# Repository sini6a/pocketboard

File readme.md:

# Pocketboard

### A Pocket-Friendly On-the-Go Keyboard 🖲️

**Pocketboard** is a compact, versatile keyboard designed for IT technicians and professionals who need a portable and efficient input device.

**NOTE:** If you are building this keyboard and want to use KMK make sure to flash MicroPython for [Adafruit Feather RP2040](https://micropython.org/download/ADAFRUIT_FEATHER_RP2040/). After flashing just copy and paste the firmware located in the `firmware/kmk` folder. I recommend using the QMK firmware instead of KMK.

## Progress List:

- [x] Firmware: Home row mods!
- [x] Firmware: Layers
- [x] Firmware: LED Control (On/Off)
- [x] Hardware & Firmware: LCD!
- [x] 3D: Case Design

## Features

- **USB Type-C Connector**: Modern and reliable connection for seamless usage.
- **Miryoku Layout**: Optimized for productivity and efficient typing.
- **LEDs and Display**: Equipped with programmable LEDs and a display which shows pressed key and small animation when idle.

## What's New?

Pocketboard builds upon the original **HandiPi** design with several upgrades and enhancements:

- **ATMega328 replaced with RP2040**: Improved performance and more flexibility with the powerful RP2040 microcontroller.
- **LEDs for Illumination**: Added for better visibility.
- **USB Type-C Connector**: Ensures ease of connectivity and compatibility with modern devices.
- **LCD Support**: Added support for an LCD display for dynamic functionality. Tested and fully operational!
- **SMD Components**: Transitioned from through-hole components to SMD for a more compact design.

## Why Pocketboard?

Pocketboard is crafted for those who are often on the move, combining portability with practicality. Whether you're debugging systems or managing configurations, this handy keyboard ensures you're always prepared and comes handy to keep in your cargo pants or in your car.

## Project Structure

The project repository is structured as follows:

- **`kicad/`**: Contains PCB design files and schematics.
- **`gerbers/`**: Includes Gerber files essential for manufacturing.
- **`fimware/qmk`**: Includes Pocketboard firmware files. This folder should be copied to `qmk_firmware/keyboards`  before compiling.
- **`fimware/kmk`**: Includes Pocketboard firmware files. This folder should be copied to your keyboard after flashing MicroPython. (Not fully implemented!)

The schematic is available in PDF format in the `kicad/` directory.

## Credits

Pocketboard is inspired by the **HandiPi** project by [brickbots](https://github.com/brickbots).

## Contributing

We welcome contributions from the community! If you’re interested in helping with development, please:

1. Open an issue to discuss your ideas or proposed changes.
2. After discussion, submit a pull request (PR) with your contribution.

Your feedback and suggestions are invaluable in making Pocketboard even better!

## Support

If you find this project useful, please consider buying from us:

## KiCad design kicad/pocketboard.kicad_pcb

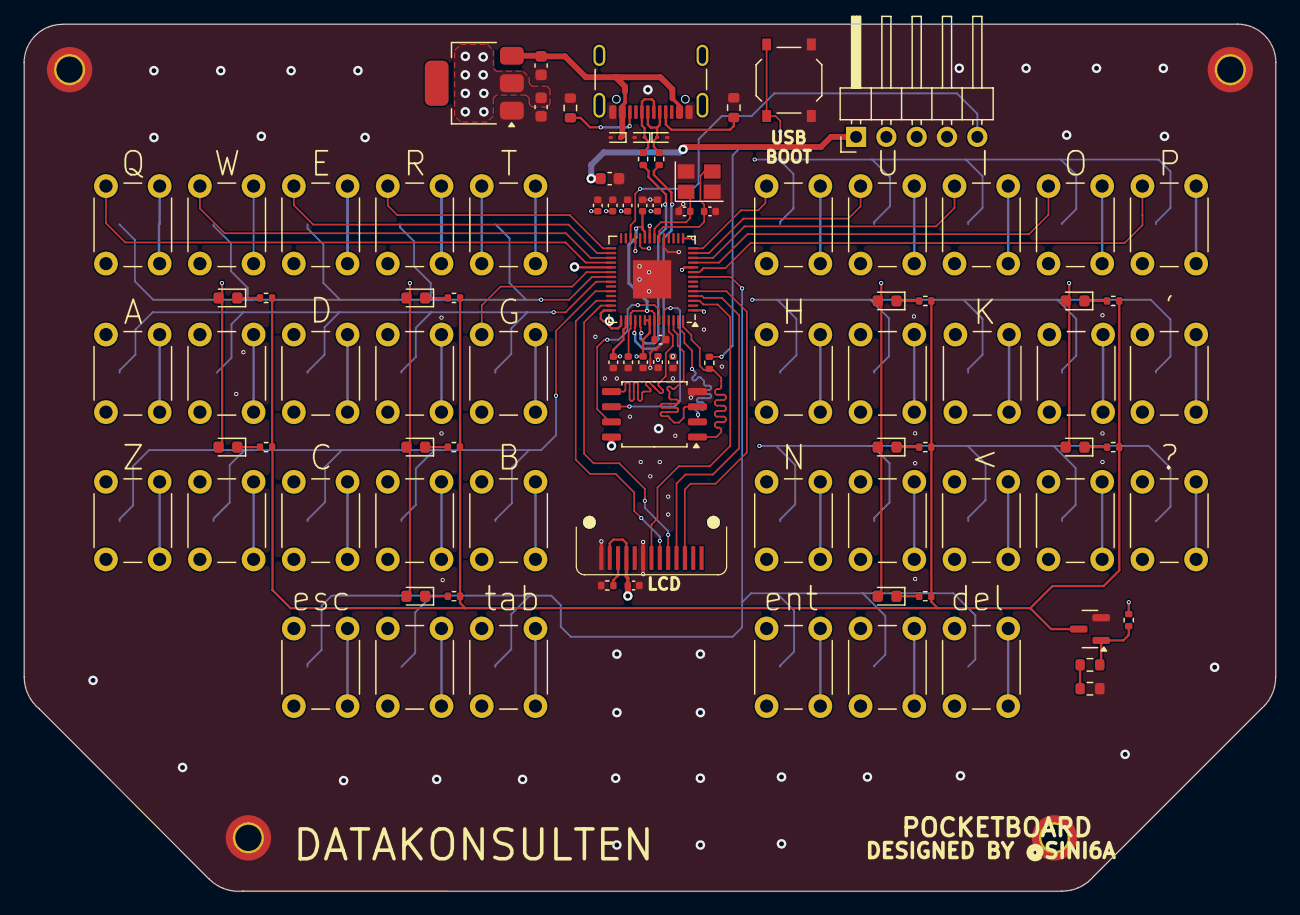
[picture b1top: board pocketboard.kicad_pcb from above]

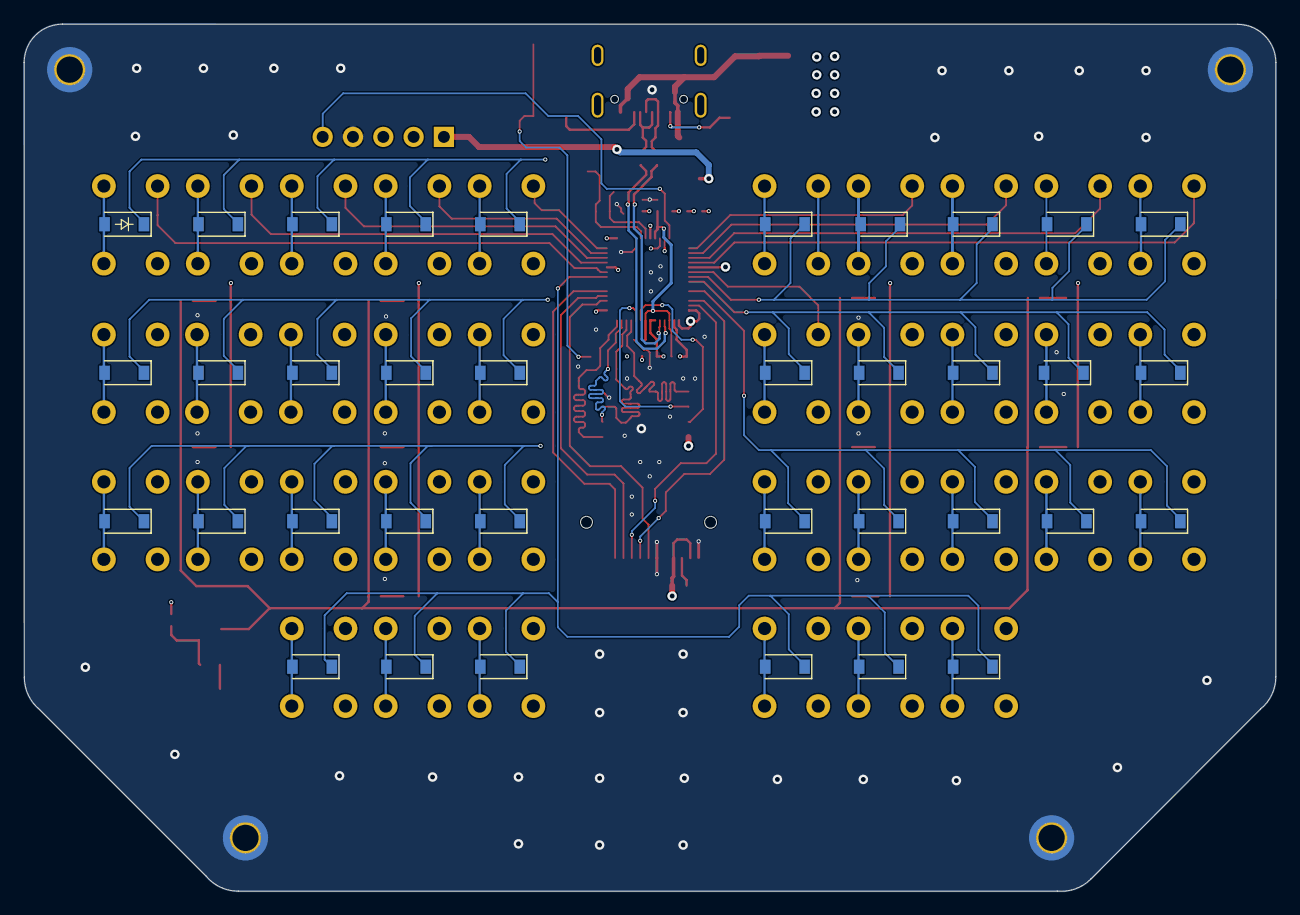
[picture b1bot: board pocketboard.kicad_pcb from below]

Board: 4 copper layers, 104.9 x 72.7 mm, 134 parts (36 on the bottom side), 92 nets.

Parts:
C201, C202, C312: 10u; C_0603_1608Metric
C301, C302, C305, C306, C307, C308, C309, C310, C311, C501: 100n; C_0402_1005Metric
C303, C304: 1u; C_0402_1005Metric
C313, C314: 33p; C_0402_1005Metric
D1, D2, D3: D_Zener; D_SOD-923
D301, D302, D303, D304, D305, D306, D307, D308, D309, D310: LED; LED_0603_1608Metric
D401, D402, D403, D404, D405, D406, D407, D408, D409, D410, D411, D412, D413, D414, D415, D416, D417, D418, D419, D420, D421, D422, D423, D424, D425, D426, D427, D428, D429, D430, D431, D432, D433, D434, D435, D436: D; D_SOD-123
H1, H2, H3, H4: Hole_Pad; MountingHole_2.2mm_M2_DIN965_Pad_TopBottom
J1: USB_C_Receptacle_USB2.0_16P; USB_C_Receptacle_GCT_USB4105-xx-A_16P_TopMnt_Horizontal
J301: DEBUG_HEADER; PinHeader_1x05_P2.54mm_Horizontal
J501: Conn_01x13; N096-1608TBBIG11-H13
Q301: 2N7002; SOT-23
R1, R2, R315, R316: 5k1; R_0603_1608Metric
R301, R302: 27R; R_0402_1005Metric
R303, R314: 1k; R_0402_1005Metric
R304, R305, R306, R307, R308, R309, R310, R311, R312, R313, R503: 33R; R_0402_1005Metric
SW401, SW402, SW403, SW404, SW405, SW406, SW407, SW408, SW409, SW410, SW411, SW412, SW413, SW414, SW415, SW416, SW417, SW418, SW419, SW420, SW421, SW422, SW423, SW424, SW425, SW426, SW427, SW428, SW429, SW430, SW431, SW432, SW433, SW434, SW435, SW436: SW_Push_Dual; SW_PUSH_6mm
SW501: SW_Push_45deg; SW_Push_1P1T_XKB_TS-1187A
U201: NCP1117-3.3_SOT223; SOT-223
U301: RP2040; QFN-56-1EP_7x7mm_P0.4mm_EP3.2x3.2mm
U302: W25Q128JVS; SOIC-8_5.23x5.23mm_P1.27mm
Y301: 12MHz 20pF; Crystal_SMD_3225-4Pin_3.2x2.5mm

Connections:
+1V1: C301.1, C302.1, C303.1, U301.23 (DVDD), U301.45 (VREG_VOUT), U301.50 (DVDD)
+3V3: C202.1, C304.1, C305.1, C306.1, C307.1, C308.1, C309.1, C310.1, C311.1, C312.1, C501.1, D301.2 (A), D302.2 (A), D303.2 (A), D304.2 (A), D305.2 (A), D306.2 (A), D307.2 (A), D308.2 (A), D309.2 (A), D310.2 (A), J301.1, J501.10, J501.12, U201.2 (VO), U301.1 (IOVDD), U301.10 (IOVDD), U301.22 (IOVDD), U301.33 (IOVDD), U301.42 (IOVDD), U301.43 (ADC_AVDD), U301.44 (VREG_IN), U301.48 (USB_VDD), U301.49 (IOVDD), U302.8 (VCC)
/Keyboard Matrix/COL0: SW401.1, SW411.1, SW421.1, U301.32 (GPIO21)
/Keyboard Matrix/COL1: SW402.1, SW412.1, SW422.1, U301.31 (GPIO20)
/Keyboard Matrix/COL2: SW403.1, SW413.1, SW423.1, SW431.1, U301.30 (GPIO19)
/Keyboard Matrix/COL3: SW404.1, SW414.1, SW424.1, SW432.1, U301.29 (GPIO18)
/Keyboard Matrix/COL4: SW405.1, SW415.1, SW425.1, SW433.1, U301.34 (GPIO22)
/Keyboard Matrix/COL5: SW406.1, SW416.1, SW426.1, SW434.1, U301.14 (GPIO11)
/Keyboard Matrix/COL6: SW407.1, SW417.1, SW427.1, SW435.1, U301.13 (GPIO10)
/Keyboard Matrix/COL7: SW408.1, SW418.1, SW428.1, SW436.1, U301.12 (GPIO9)
/Keyboard Matrix/COL8: SW409.1, SW419.1, SW429.1, U301.11 (GPIO8)
/Keyboard Matrix/COL9: SW410.1, SW420.1, SW430.1, U301.9 (GPIO7)
/Keyboard Matrix/ROW0: D401.1 (K), D402.1 (K), D403.1 (K), D404.1 (K), D405.1 (K), D406.1 (K), D407.1 (K), D408.1 (K), D409.1 (K), D410.1 (K), U301.35 (GPIO23)
/Keyboard Matrix/ROW1: D411.1 (K), D412.1 (K), D413.1 (K), D414.1 (K), D415.1 (K), D416.1 (K), D417.1 (K), D418.1 (K), D419.1 (K), D420.1 (K), U301.36 (GPIO24)
/Keyboard Matrix/ROW2: D421.1 (K), D422.1 (K), D423.1 (K), D424.1 (K), D425.1 (K), D426.1 (K), D427.1 (K), D428.1 (K), D429.1 (K), D430.1 (K), U301.38 (GPIO26_ADC0)
/Keyboard Matrix/ROW3: D431.1 (K), D432.1 (K), D433.1 (K), D434.1 (K), D435.1 (K), D436.1 (K), U301.8 (GPIO6)
/LCD/D/C: J501.5, U301.41 (GPIO29_ADC3)
/LCD/LEDK: J501.11, R503.2
/LCD/SCL: J501.4, U301.4 (GPIO2)
/LCD/SDA: J501.3, U301.5 (GPIO3)
/LCD/~CS: J501.7, U301.3 (GPIO1)
/LCD/~RESET: J501.6, U301.40 (GPIO28_ADC2)
/Microcontroller/QSPI_SCLK: U301.52 (QSPI_SCLK), U302.6 (CLK)
/Microcontroller/QSPI_SD0: U301.53 (QSPI_SD0), U302.5 (DI(IO0))
/Microcontroller/QSPI_SD1: U301.55 (QSPI_SD1), U302.2 (DO(IO1))
/Microcontroller/QSPI_SD2: U301.54 (QSPI_SD2), U302.3 (IO2)
/Microcontroller/QSPI_SD3: U301.51 (QSPI_SD3), U302.7 (IO3)
/Microcontroller/QSPI_SS: R303.1, U301.56 (QSPI_SS), U302.1 (~CS)
/Microcontroller/RST: J301.5, U301.26 (RUN)
/Microcontroller/SWCLK: J301.3, U301.24 (SWCLK)
/Microcontroller/SWD: J301.2, U301.25 (SWD)
/Microcontroller/USB_DN: D1.1 (K), J1.A7 (D-), J1.B7 (D-), R302.2
/Microcontroller/USB_DP: D2.1 (K), J1.A6 (D+), J1.B6 (D+), R301.2
/Microcontroller/~USB_BOOT: R303.2, SW501.2
GND: C201.2, C202.2, C301.2, C302.2, C303.2, C304.2, C305.2, C306.2, C307.2, C308.2, C309.2, C310.2, C311.2, C312.2, C313.1, C314.1, C501.2, D1.2 (A), D2.2 (A), D3.2 (A), H1.1, H2.1, H3.1, H4.1, J1.A1 (GND), J1.A12 (GND), J1.B1 (GND), J1.B12 (GND), J301.4, J501.8, J501.13, Q301.2 (S), R1.1, R2.1, R316.2, R503.1, SW501.1, U201.1 (GND), U301.19 (TESTEN), U301.57 (GND), U302.4 (GND), Y301.2, Y301.4
LED_SW: R314.2, U301.15 (GPIO12)
unnamed: D301.1 (K), R304.1
unnamed: D302.1 (K), R305.1
unnamed: D303.1 (K), R306.1
unnamed: D304.1 (K), R307.1
unnamed: D305.1 (K), R308.1
unnamed: D306.1 (K), R309.1
unnamed: D307.1 (K), R310.1
unnamed: D308.1 (K), R311.1
unnamed: D309.1 (K), R312.1
unnamed: D310.1 (K), R313.1
unnamed: D401.2 (A), SW401.2
unnamed: D402.2 (A), SW402.2
unnamed: D403.2 (A), SW403.2
unnamed: D404.2 (A), SW404.2
unnamed: D405.2 (A), SW405.2
unnamed: D406.2 (A), SW406.2
unnamed: D407.2 (A), SW407.2
unnamed: D408.2 (A), SW408.2
unnamed: D409.2 (A), SW409.2
unnamed: D410.2 (A), SW410.2
unnamed: D411.2 (A), SW411.2
unnamed: D412.2 (A), SW412.2
unnamed: D413.2 (A), SW413.2
unnamed: D414.2 (A), SW414.2
unnamed: D415.2 (A), SW415.2
unnamed: D416.2 (A), SW416.2
unnamed: D417.2 (A), SW417.2
unnamed: D418.2 (A), SW418.2
unnamed: D419.2 (A), SW419.2
unnamed: D420.2 (A), SW420.2
unnamed: D421.2 (A), SW421.2
unnamed: D422.2 (A), SW422.2
unnamed: D423.2 (A), SW423.2
unnamed: D424.2 (A), SW424.2
unnamed: D425.2 (A), SW425.2
unnamed: D426.2 (A), SW426.2
unnamed: D427.2 (A), SW427.2
unnamed: D428.2 (A), SW428.2
unnamed: D429.2 (A), SW429.2
unnamed: D430.2 (A), SW430.2
unnamed: D431.2 (A), SW431.2
unnamed: D432.2 (A), SW432.2
unnamed: D433.2 (A), SW433.2
unnamed: D434.2 (A), SW434.2
unnamed: D435.2 (A), SW435.2
unnamed: D436.2 (A), SW436.2
unnamed: J1.A5 (CC1), R1.2
unnamed: J1.B5 (CC2), R2.2
unnamed: Q301.3 (D), R304.2, R305.2, R306.2, R307.2, R308.2, R309.2, R310.2, R311.2, R312.2, R313.2
unnamed: Q301.1 (G), R314.1, R315.1
unnamed: R315.2, R316.1
unnamed: R302.1, U301.46 (USB_DM)
unnamed: R301.1, U301.47 (USB_DP)
unnamed: C313.2, U301.20 (XIN), Y301.3
unnamed: C314.2, U301.21 (XOUT), Y301.1
VBUS: C201.1, D3.1 (K), J1.A4 (VBUS), J1.A9 (VBUS), J1.B4 (VBUS), J1.B9 (VBUS), U201.3 (VI)

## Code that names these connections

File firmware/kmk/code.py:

import microcontroller.pin as board # type: ignore
import digitalio
from kmk.kmk_keyboard import KMKKeyboard
from kmk.keys import KC
from kmk.scanners import DiodeOrientation
from kmk.modules.layers import Layers

print("Starting")

keyboard = KMKKeyboard()
keyboard.modules.append(Layers())

# Define the GPIO pin you want to control
pin_to_toggle = digitalio.DigitalInOut(board.GPIO12)  # Replace with your pin number
pin_to_toggle.direction = digitalio.Direction.OUTPUT
pin_to_toggle.value = True  # Start with the pin LOW

# Define your keyboard matrix and configuration
keyboard.col_pins = (
    board.GPIO21, board.GPIO20, board.GPIO19, board.GPIO18, board.GPIO22,
    board.GPIO11, board.GPIO10, board.GPIO9, board.GPIO8, board.GPIO7
)
keyboard.row_pins = (
    board.GPIO23, board.GPIO24, board.GPIO26, board.GPIO6
)
keyboard.diode_orientation = DiodeOrientation.ROW2COL

# Define the keymap
keyboard.keymap = [
    [
        KC.Q                , KC.W                , KC.E               , KC.R               , KC.T                  , KC.Y              , KC.U               , KC.I               , KC.O                , KC.P,
        KC.A                , KC.S                , KC.D               , KC.F               , KC.G                  , KC.H              , KC.J               , KC.K               , KC.L                , KC.SCLN,
        KC.Z                , KC.X                , KC.C               , KC.V               , KC.B                  , KC.N              , KC.M               , KC.COMMA           , KC.DOT              , KC.SLSH,
        KC.NO               , KC.NO               , KC.ESC             , KC.SPC             , KC.TAB                , KC.ENTER          , KC.BACKSPACE       , KC.DEL             , KC.NO               , KC.NO
    ],
]

if __name__ == '__main__':
    keyboard.go()

"""     [1] = LAYOUT_qwerty( // nav layer
        KC_NO,      KC_NO,   KC_NO,   KC_NO,   KC_NO,   KC_NO,         KC_NO,   KC_NO,   KC_NO,   KC_NO,   KC_NO,             KC_NO,
        KC_NO,         KC_NO,   KC_NO,   KC_NO,   KC_NO,   KC_NO,         KC_AGIN,   KC_PASTE,   KC_COPY,   KC_CUT,   KC_UNDO,             KC_NO,
        KC_NO,  KC_LGUI,   KC_LALT,   KC_LCTL,   KC_LSFT,   KC_NO,         KC_CAPS,   KC_LEFT,   KC_DOWN,   KC_UP,   KC_RIGHT,     KC_NO,
        KC_NO,   KC_NO,   KC_NO,   KC_NO,   KC_NO,   KC_NO,         KC_INS,   KC_HOME,   KC_PAGE_DOWN,   KC_PAGE_UP,   KC_END,    KC_NO,
                                   KC_NO, KC_NO, KC_NO,         KC_ENTER, KC_BACKSPACE, KC_DELETE
    ),
    [2] = LAYOUT_qwerty( // function layer
        QK_BOOT,      KC_F1,   KC_F2,   KC_F3,   KC_F4,   KC_F5,         KC_F6,   KC_F7,   KC_F8,   KC_F9,   KC_F10,             KC_NO,
        KC_NO,     KC_F12,   KC_F7,   KC_F8,   KC_F9,   KC_PSCR,         KC_NO,   KC_NO,   KC_NO,   KC_F11,   KC_F12,             KC_NO,
        KC_NO,     KC_F11,   KC_F4,   KC_F5,   KC_F6,   KC_SCRL,         KC_NO,   KC_RSFT,   KC_RCTL,   KC_RALT,   KC_RGUI,     KC_NO,
        KC_NO,     KC_F10,   KC_F1,   KC_F2,   KC_F3,   KC_PAUS,         KC_NO,   KC_NO,   KC_NO,   KC_NO,   KC_NO,    KC_NO,
                                         KC_APP, KC_SPC, KC_TAB,         KC_NO, KC_NO, KC_NO
    ),
    [3] = LAYOUT_qwerty( // number layer
        KC_NO,      KC_NO,   KC_NO,   KC_NO,   KC_NO,   KC_NO,         KC_NO,   KC_NO,   KC_NO,   KC_NO,   KC_NO,             KC_NO,
        KC_NO,     KC_LBRC,   KC_7,   KC_8,   KC_9,   KC_RCBR,         KC_NO,   KC_NO,   KC_NO,   KC_NO,   KC_NO,             KC_NO,
        KC_NO,     KC_SCLN,   KC_4,   KC_5,   KC_6,   KC_EQL,         KC_NO,   KC_RSFT,   KC_RCTL,   KC_RALT,   KC_RGUI,     KC_NO,
        KC_NO,     KC_COMM,   KC_1,   KC_2,   KC_3,   KC_BSLS,         KC_NO,   KC_NO,   KC_NO,   KC_NO,   KC_NO,    KC_NO,
                                         KC_DOT, KC_0, KC_MINUS,         KC_NO, KC_NO, KC_NO
    ),
    [4] = LAYOUT_qwerty( // symbol layer
        KC_NO,      KC_NO,   KC_NO,   KC_NO,   KC_NO,   KC_NO,         KC_NO,   KC_NO,   KC_NO,   KC_NO,   KC_NO,             KC_NO,
        KC_NO,     KC_LCBR,   KC_AMPR,   KC_ASTR,   KC_LPRN,   KC_RCBR,         KC_NO,   KC_NO,   KC_NO,   KC_NO,   KC_NO,             KC_NO,
        KC_NO,     KC_COLN,   KC_DLR,   KC_PERC,   KC_CIRC,   KC_PLUS,         KC_NO,   KC_RSFT,   KC_RCTL,   KC_RALT,   KC_RGUI,     KC_NO,
        KC_NO,     KC_TILD,   KC_EXLM,   KC_AT,   KC_HASH,   KC_PIPE,         KC_NO,   KC_NO,   KC_NO,   KC_NO,   KC_NO,    KC_NO,
                                         KC_LPRN, KC_RPRN, KC_UNDS,         KC_NO, KC_NO, KC_NO
    ),
    [5] = LAYOUT_qwerty( // media layer
        KC_NO,      KC_NO,   KC_NO,   KC_NO,   KC_NO,   KC_NO,         KC_NO,   KC_NO,   KC_NO,   KC_NO,   KC_NO,             KC_NO,
        KC_NO,     KC_NO,   KC_NO,   KC_NO,   KC_NO,   KC_NO,         RGB_TOG,   RGB_MOD,   RGB_HUI,   RGB_SAI,   RGB_VAI,             KC_NO,
        KC_NO,     KC_LGUI,   KC_LALT,   KC_LCTL,   KC_LSFT,   KC_NO,         KC_NO,   KC_MPRV,   KC_VOLD,   KC_VOLU,   KC_MNXT,     KC_NO,
        KC_NO,     KC_NO,   KC_NO,   KC_NO,   KC_NO,   KC_NO,         KC_NO,   KC_NO,   KC_NO,   KC_NO,   KC_NO,             KC_NO,
                                         KC_NO, KC_NO, KC_NO,         KC_MSTP, KC_MPLY, KC_MUTE
    ),
    [6] = LAYOUT_qwerty( // mouse layer
        KC_NO,      KC_NO,   KC_NO,   KC_NO,   KC_NO,   KC_NO,         KC_NO,   KC_NO,   KC_NO,   KC_NO,   KC_NO,             KC_NO,
        KC_NO,         KC_NO,   KC_NO,   KC_NO,   KC_NO,   KC_NO,         KC_AGIN,   KC_PASTE,   KC_COPY,   KC_CUT,   KC_UNDO,             KC_NO,
        KC_NO,  KC_LGUI,   KC_LALT,   KC_LCTL,   KC_LSFT,   KC_NO,         KC_NO,   KC_MS_L,   KC_MS_D,   KC_MS_U,   KC_MS_R,     KC_NO,
        KC_NO,   KC_NO,   KC_NO,   KC_NO,   KC_NO,   KC_NO,         KC_NO,   KC_WH_L,   KC_WH_D,   KC_WH_U,   KC_WH_R,    KC_NO,
                                   KC_NO, KC_NO, KC_NO,         KC_BTN2, KC_BTN1, KC_BTN3
    )
 """

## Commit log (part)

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2025-01-21 initial release
2025-05-08 Updated to KiCad 9
2025-05-08 Added qmk firmware
2025-06-22 changed from rp2040 to nrf
2025-07-08 board routed
2025-08-27 added zmk-config submodule
2025-08-27 added readme.md in firmware & updated readme.md
2025-08-27 deleted legacy code for RP2040
2025-09-05 updated undefined_netclass: error
2025-09-05 added few more images
